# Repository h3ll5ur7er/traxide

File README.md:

# traxide

*trace* + *oxide*: a fast, dependency-free PCB autorouter for KiCad and every tool that speaks Specctra DSN: a modern alternative to Freerouting, written in Rust, using every CPU core and, when present, the GPU.

> traxide is young: it routes a 4-layer keyboard with an RP2350 completely in seconds, and KiCad 10's DRC finds the result clean, while Freerouting takes minutes and leaves violations. It reads KiCad's board files and Specctra DSN, and has met few boards yet. See the [benchmarks](docs/Benchmarks.md).

## Try it

Download traxide and its KiCad plugin from the repository's **Releases**: archives for Linux, Windows (x86-64 and ARM64 each) and macOS (universal), with nothing else to install, and a KiCad package for each. Between releases, every push builds the same in the **Binaries** workflow under the *Actions* tab. Or build it:

```bash
cargo build --release
# A KiCad 9 or 10 board, with the rules of its project: writes board.routed.kicad_pcb
target/release/traxide route board.kicad_pcb
# Or, as with Freerouting: in KiCad, File → Export → Specctra DSN, then
target/release/traxide route board.dsn        # writes board.ses, on all cores
target/release/traxide route --help           # profiles, threads, output
target/release/traxide route board.dsn --time-limit 60   # stop negotiating after a minute
target/release/traxide route board.dsn --profile fast       # routed once: a quick first look
target/release/traxide route board.kicad_pcb --reroute-existing   # route the board's unlocked tracks again too
target/release/traxide route board.kicad_pcb --net USB_D_P --net USB_D_N   # route only these nets
target/release/traxide check board.dsn board.ses   # complete? rules broken?
# The same verdict as a DRC report in KiCad's JSON format (route takes --drc too)
target/release/traxide check board.dsn board.ses --drc board.drc.json
# In place of Freerouting: the same arguments, -drc report.json included
target/release/traxide freerouting -de board.dsn -do board.ses
# In KiCad: File → Import → Specctra Session
```

### From inside KiCad

traxide's KiCad plugin adds a **Route board** button to the PCB editor's toolbar (KiCad 9 and 10). It routes every unrouted connection of the open board and adds the routes as one step: *Edit → Undo traxide: route* takes them all back. Its second button, **Route selected nets** (the blue one), routes only the nets of what is selected: tracks, vias, pads, footprints or zones; the rest of the board is kept as it is. The third, **Optimise** (the amber one), pulls the board's own unlocked tracks tight, routed by traxide, by hand or by another router: shorter, with fewer corners, nothing they join coming apart; arcs and locked tracks stay as they are. It changes nothing that would break a rule, and *Edit → Undo traxide: optimise* takes it back. The rules come from KiCad's net classes and the project's files. On a board with copper zones traxide then refills them around the routes, a step of its own, so taking the routes back takes two undos.

1. **Enable KiCad's API first**: *Preferences → Preferences… → Plugins → Enable KiCad API*. It is off by default, and **without it KiCad shows no traxide button at all**.
2. Download the KiCad package for your platform (`traxide-kicad-<version>-<platform>.zip`) from the Releases and install it with *Plugin and Content Manager → Install from File…*.
3. Restart the PCB editor: the button appears in its top toolbar. In KiCad 10, traxide's report (how much it routed, and what it could not) appears under the warning sign at the right end of the status bar; KiCad 9 shows the routes but not the report.

The package carries the traxide binary itself; there is no Python. From a terminal, `traxide route --kicad` does what the button does, `traxide route --selected` what the second one does, and `traxide optimise --kicad` the third; `traxide optimise BOARD.kicad_pcb` writes an optimised copy, `BOARD.optimised.kicad_pcb`, beside a board file.

A copy of the binary named `freerouting` (`freerouting.exe` on Windows) takes Freerouting's arguments too, for tools that run Freerouting.

- **Wiki**: [`docs/Home.md`](docs/Home.md). Covers [research](docs/Research.md), [architecture](docs/Architecture.md) (iDesign, decomposed by volatility) and the [project plan](docs/Project-plan.md).
- **Tasks**: [`tasks/`](tasks), one Markdown file per task, grouped by milestone.

Both are plain files managed with [Genbeya](https://github.com/genbeya/genbeya). Open this folder in Genbeya to get the wiki and the board with live references.

## License

Licensed under either of

- Apache License, Version 2.0 ([LICENSE-APACHE](LICENSE-APACHE))
- MIT license ([LICENSE-MIT](LICENSE-MIT))

at your option.

Unless you explicitly state otherwise, any contribution intentionally submitted for inclusion in traxide by you, as defined in the Apache-2.0 license, shall be dual licensed as above, without any additional terms or conditions. traxide is written clean-room: see [Clean-room rules](docs/Development.md#clean-room-rules).

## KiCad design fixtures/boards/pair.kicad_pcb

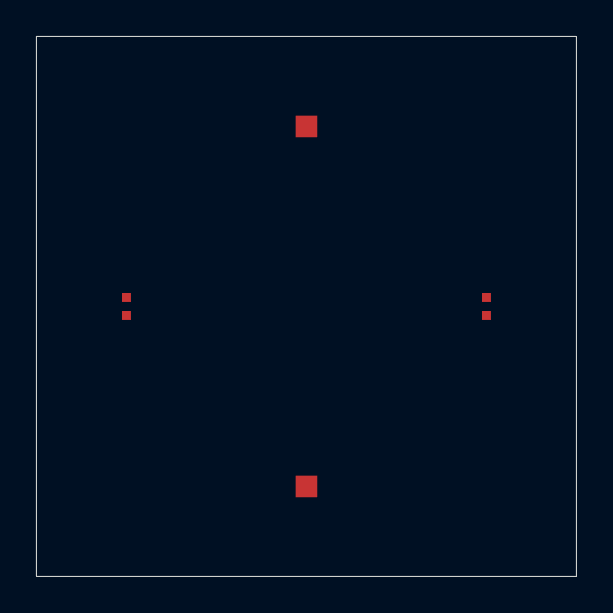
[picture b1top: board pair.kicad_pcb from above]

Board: 2 copper layers, 30.0 x 30.0 mm, 4 parts (0 on the bottom side), 3 nets, no tracks yet.

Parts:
J1, J2: TP
TP1, TP2: TP

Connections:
ACROSS: TP1.1, TP2.1
USB_D_N: J1.2, J2.2
USB_D_P: J1.1, J2.1
